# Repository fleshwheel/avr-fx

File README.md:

# avr-fx
audio effects design based on atmega328p

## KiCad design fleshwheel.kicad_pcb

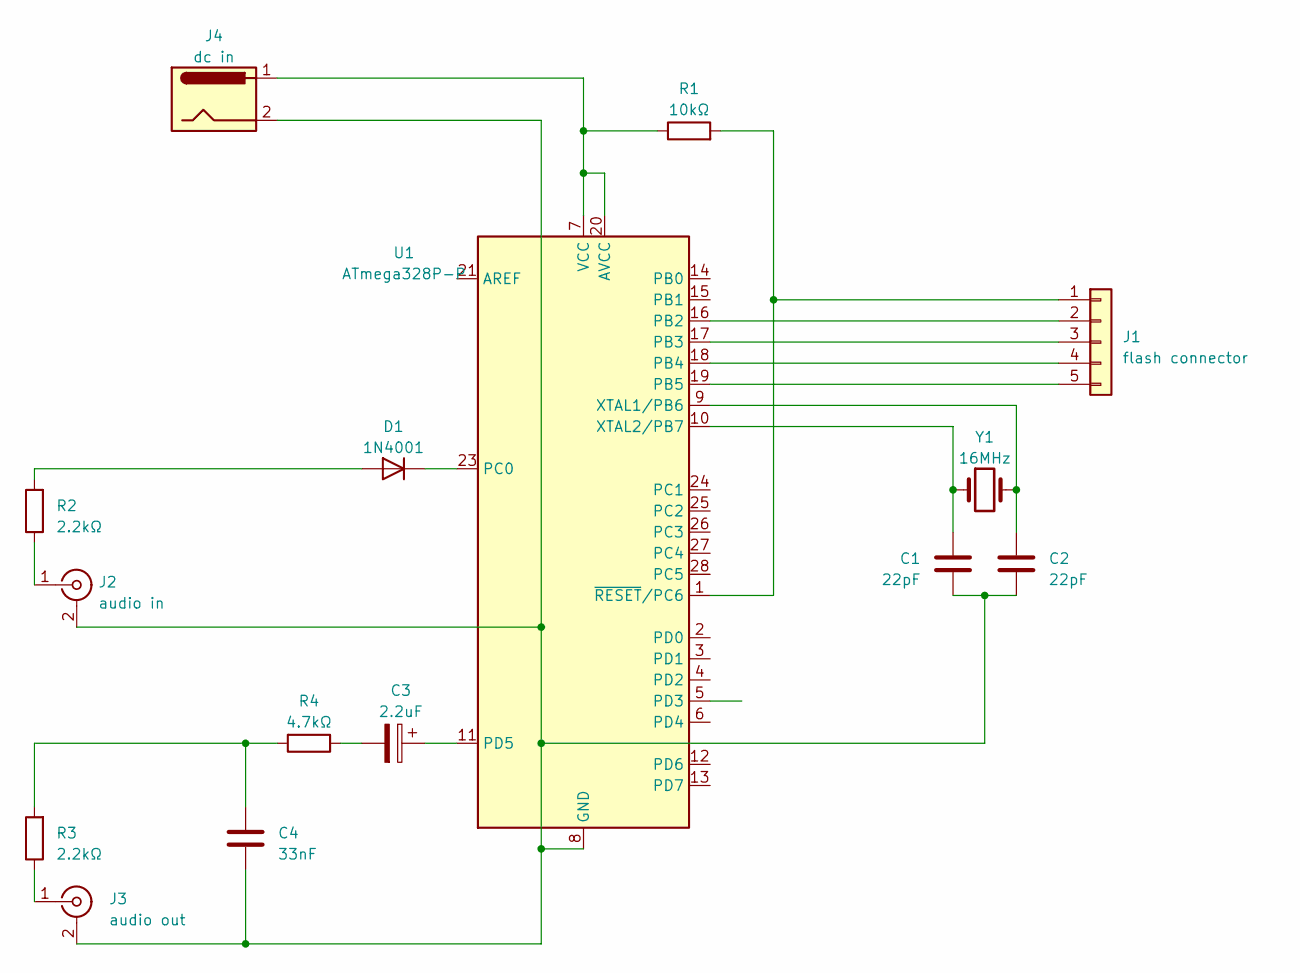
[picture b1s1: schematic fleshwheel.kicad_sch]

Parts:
C1, C2: 22pF; C_Axial_L3.8mm_D2.6mm_P7.50mm_Horizontal
C3: 2.2uF; CP_Radial_D4.0mm_P1.50mm
C4: 33nF; C_Axial_L3.8mm_D2.6mm_P7.50mm_Horizontal
D1: 1N4001; D_DO-41_SOD81_P10.16mm_Horizontal
J1: flash connector; PinHeader_1x05_P2.54mm_Vertical
J2: audio in; BarrelJack_CUI_PJ-063AH_Horizontal
J3: audio out; BarrelJack_CUI_PJ-063AH_Horizontal
J4: dc in; BarrelJack_Kycon_KLDX-0202-xC_Horizontal
R1: 10kΩ; R_Axial_DIN0207_L6.3mm_D2.5mm_P7.62mm_Horizontal
R2, R3: 2.2kΩ; R_Axial_DIN0207_L6.3mm_D2.5mm_P7.62mm_Horizontal
R4: 4.7kΩ; R_Axial_DIN0207_L6.3mm_D2.5mm_P7.62mm_Horizontal
U1: ATmega328P-P; DIP-28_W7.62mm
Y1: 16MHz; Crystal_HC52-6mm_Vertical

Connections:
unnamed: C3.2, R4.1
unnamed: C4.1, R3.2, R4.2
unnamed: D1.2 (A), R2.2
unnamed: D1.1 (K), U1.23 (PC0)
unnamed: J1.1, R1.2, U1.1 (~RESET/PC6)
unnamed: J1.2, U1.16 (PB2)
unnamed: J1.3, U1.17 (PB3)
unnamed: J1.4, U1.18 (PB4)
unnamed: J1.5, U1.19 (PB5)
unnamed: C1.2, C2.2, C4.2, J2.2 (Ext), J3.2 (Ext), J4.2, U1.8 (GND), U1.22 (GND)
unnamed: J2.1 (In), R2.1
unnamed: J3.1 (In), R3.1
unnamed: J4.1, R1.1, U1.7 (VCC), U1.20 (AVCC)
unnamed: C3.1, U1.11 (PD5)
unnamed: C2.1, U1.9 (XTAL1/PB6), Y1.2
unnamed: C1.1, U1.10 (XTAL2/PB7), Y1.1

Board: 2 copper layers, 15 parts (0 on the bottom side), 16 nets, no tracks yet.

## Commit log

2023-04-18 cheeky; fed up
